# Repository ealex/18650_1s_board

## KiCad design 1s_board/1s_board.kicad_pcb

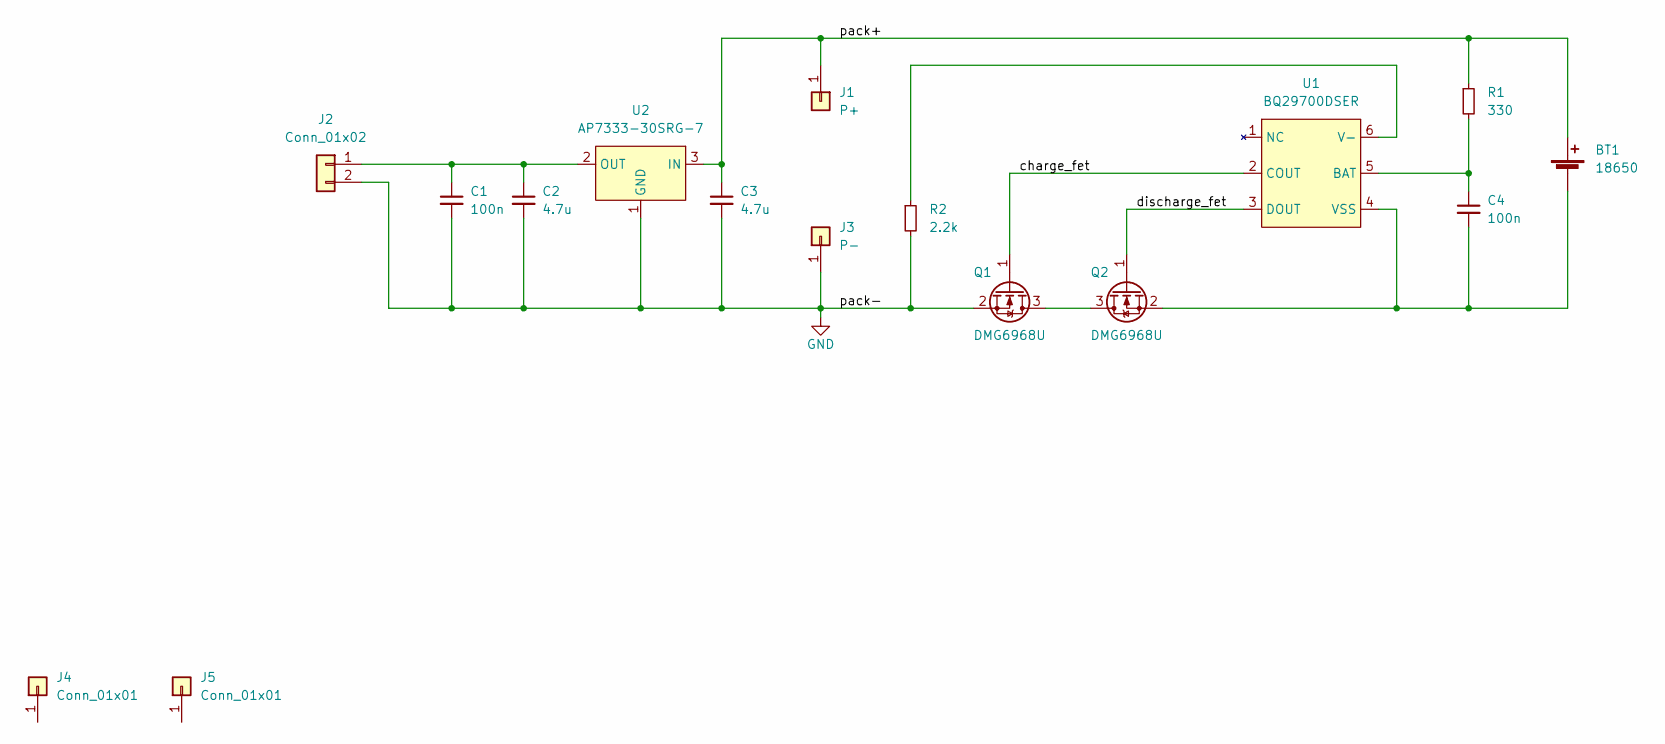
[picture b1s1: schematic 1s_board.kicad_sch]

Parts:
BT1: 18650; KEYSTONE-534-1043
C1, C4: 100n; C_1206_3216Metric
C2, C3: 4.7u; C_1206_3216Metric
J1: P+; TestPoint_Loop_D2.60mm_Drill0.9mm_Beaded
J2: Conn_01x02; JST_PH_B2B-PH-K_1x02_P2.00mm_Vertical
J3: P-; TestPoint_Loop_D2.60mm_Drill0.9mm_Beaded
J4, J5: Conn_01x01; MountingHole_3.2mm_M3
Q1, Q2: DMG6968U; SOT-23
R1: 330; R_1206_3216Metric
R2: 2.2k; R_1206_3216Metric
U1: BQ29700DSER
U2: AP7333-30SRG-7; SOT-23

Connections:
/charge_fet: Q1.1 (G), U1.2 (COUT)
/discharge_fet: Q2.1 (G), U1.3 (DOUT)
/pack+: BT1.1 (+), C3.1, J1.1, R1.1, U2.3 (IN)
GND: C1.2, C2.2, C3.2, J2.2, J3.1, Q1.2 (S), R2.2, U2.1 (GND)
unnamed: BT1.2 (-), C4.2, Q2.2 (S), U1.4 (VSS)
unnamed: C1.1, C2.1, J2.1, U2.2 (OUT)
unnamed: C4.1, R1.2, U1.5 (BAT)
unnamed: Q1.3 (D), Q2.3 (D)
unnamed: R2.1, U1.6 (V-)

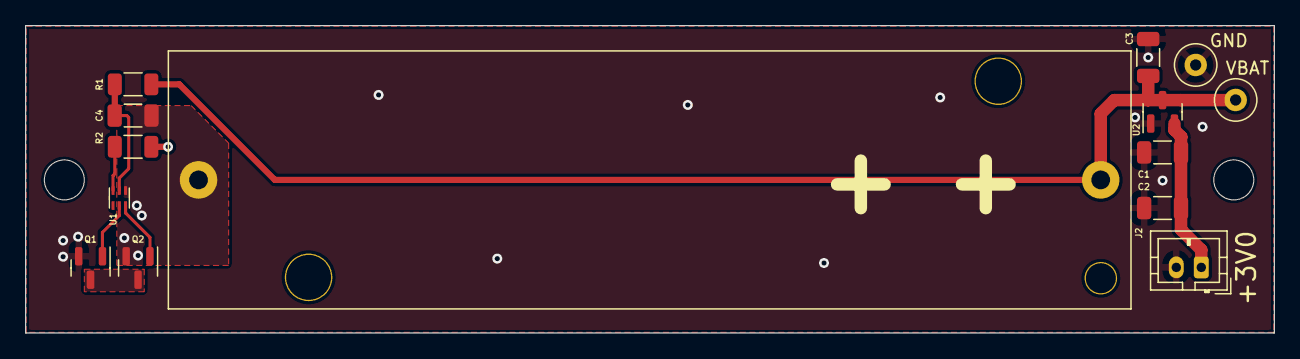
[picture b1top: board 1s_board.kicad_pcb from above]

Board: 2 copper layers, 99.9 x 24.6 mm, 16 parts (0 on the bottom side), 9 nets.

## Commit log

2024-10-22 add datasheets
2024-10-22 add schematic and layout
2024-10-22 Add pdf schematic
